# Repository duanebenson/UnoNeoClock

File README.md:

# UnoNeoClock
Arduino compatible NeoPixel clock design

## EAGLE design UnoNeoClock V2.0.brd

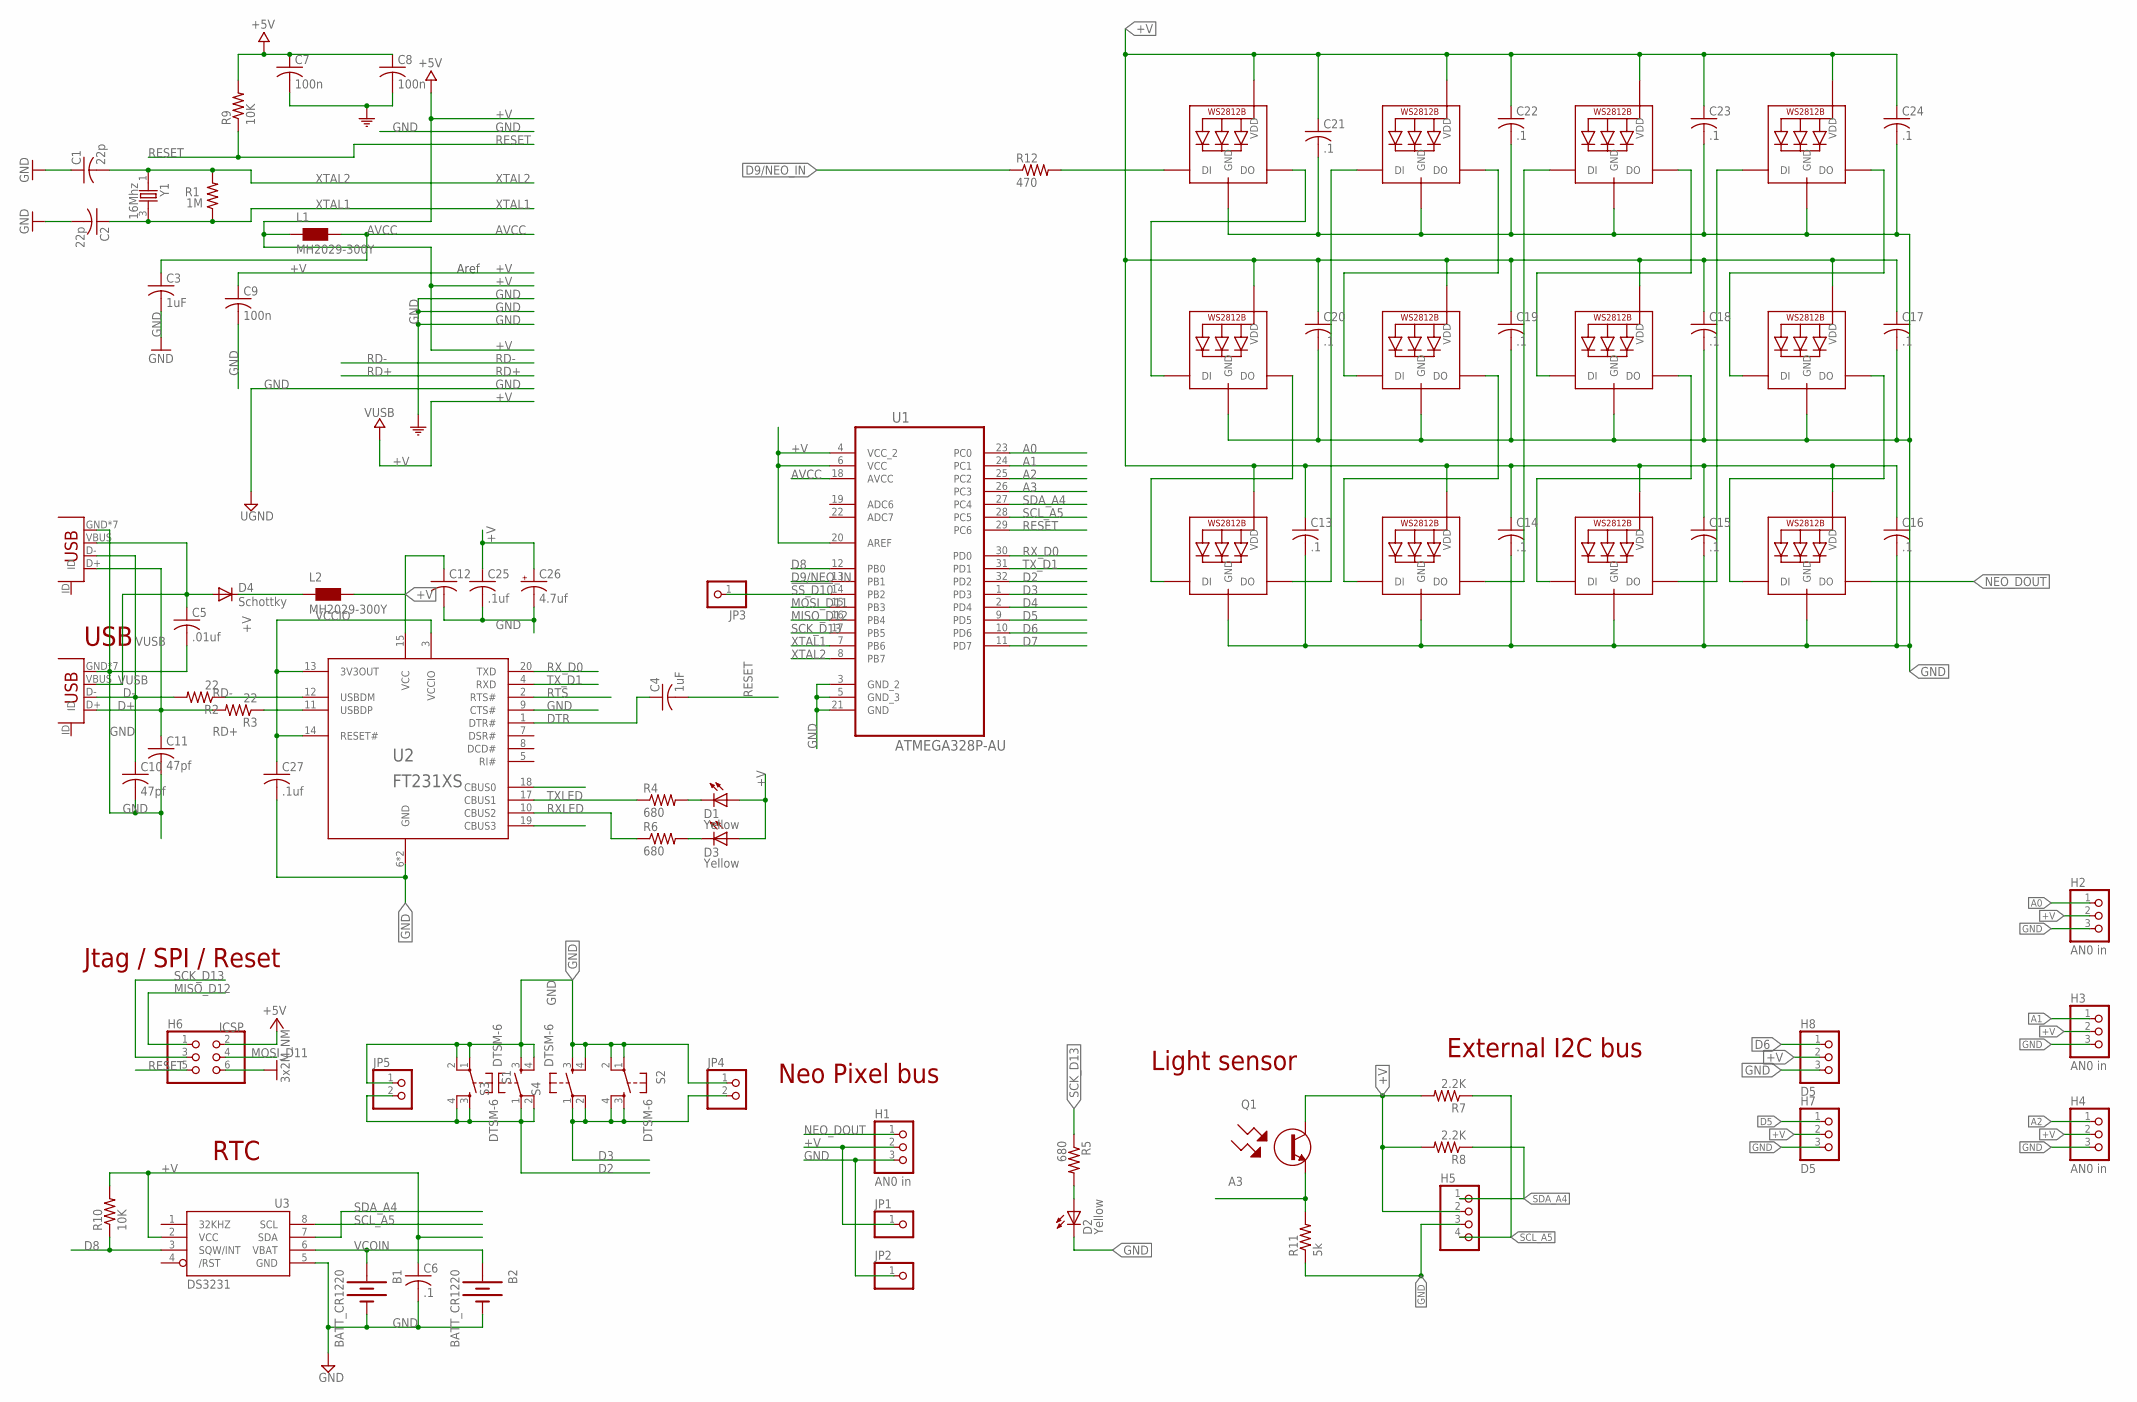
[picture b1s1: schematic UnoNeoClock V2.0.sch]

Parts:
B1, B2: BATT_CR1220; BATT_CR1220_HOLDER_SMT
C1, C2: 22p; C0805K
C3, C4: 1uF; C0805K
C5: .01uf; C0805K
C6, C13, C14, C15, C16, C17, C18, C19, C20, C21, C22, C23, C24: .1; C0805K
C7, C8, C9: 100n; C0805K
C10, C11: 47pf; C0805K
C12: C-USC1206K; C1206K
C25, C27: .1uf; C0805K
C26: 4.7uf; SMC_P
D1, D2, D3: Yellow; CHIP-LED0805
D4: Schottky; SOD123
H1, H2, H3, H4: AN0 in; 1X03-S
H5: PINHD-1X04_2.54-S; 1X04-S
H6: ICSP; 2X03
H7, H8: D5; 1X03-S
J1, J2: USB-MICRO-B-SMT/TH; USB-MICRO-B-SMT
JP1, JP2, JP3: PINHD-1X1; 1X01
JP4, JP5: PINHD-1X02_2.54-S; 1X02-S
L1, L2: MH2029-300Y; 0805
LED1, LED2, LED3, LED4, LED5, LED6, LED7, LED8, LED9, LED10, LED11, LED12: WS2812B5050; WS2812B
Q1: KDT00030FSTR; PT0603
R1: 1M; R0805
R2, R3: 22; R0805
R4, R5, R6: 680; R0805
R7, R8: 2.2K; R0805
R9, R10: 10K; R0805
R11: 5k; R0805
R12: 470; R0805
S1, S2, S3, S4: DTSM-6
U1: ATMEGA328P-AU; QFP80P900X900X120-32N
U2: FT231XS; SSOP20
U3: DS3231; SOIC8
Y1: 16Mhz; 3X5XTAL-SMT

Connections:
!SS_D10: JP3.1, U1.14 (PB2)
+V: C6.1, C7.1, C8.1, C9.1, C12.1, C13.1, C14.1, C15.1, C16.1, C17.1, C18.1, C19.1, C20.1, C21.1, C22.1, C23.1, C24.1, C25.1, C26.+, D1.A, D3.A, H1.2, H2.2, H3.2, H4.2, H5.2, H6.2, H7.2, H8.2, JP1.1, L1.1, L2.2, LED1.1-VDD (VDD), LED2.1-VDD (VDD), LED3.1-VDD (VDD), LED4.1-VDD (VDD), LED5.1-VDD (VDD), LED6.1-VDD (VDD), LED7.1-VDD (VDD), LED8.1-VDD (VDD), LED9.1-VDD (VDD), LED10.1-VDD (VDD), LED11.1-VDD (VDD), LED12.1-VDD (VDD), Q1.C, R7.2, R8.2, R9.2, R10.2, U1.4 (VCC_2), U1.6 (VCC), U1.20 (AREF), U2.15 (VCC), U3.2 (VCC)
A0: H2.1, U1.23 (PC0)
A1: H3.1, U1.24 (PC1)
A2: H4.1, U1.25 (PC2)
A3: Q1.E, R11.2, U1.26 (PC3)
AVCC: C3.1, L1.2, U1.18 (AVCC)
D2: JP5.2, S1.3, S1.4, S3.1, S3.2, U1.32 (PD2)
D3: JP4.2, S2.3, S2.4, S4.1, S4.2, U1.1 (PD3)
D4: U1.2 (PD4)
D5: H7.1, U1.9 (PD5)
D6: H8.1, U1.10 (PD6)
D7: U1.11 (PD7)
D8: R10.1, U1.12 (PB0), U3.3 (SQW/INT)
D9/NEO_IN: R12.1, U1.13 (PB1)
D+: C11.1, J1.D+, J2.D+, R3.2
D-: C10.1, J1.D-, J2.D-, R2.2
DTR: C4.1, U2.1 (DTR#)
GND: B1.1 (-), B2.1 (-), C1.1, C2.2, C3.2, C5.2, C6.2, C7.2, C8.2, C9.2, C10.2, C11.2, C12.2, C13.2, C14.2, C15.2, C16.2, C17.2, C18.2, C19.2, C20.2, C21.2, C22.2, C23.2, C24.2, C25.2, C26.-, C27.2, D2.C, H1.3, H2.3, H3.3, H4.3, H5.3, H6.6, H7.3, H8.3, J1.GND, J1.GND@1 (GND), J1.GND@2 (GND), J1.GND@3 (GND), J1.GND@4 (GND), J1.GND@5 (GND), J1.GND@6 (GND), J2.GND, J2.GND@1 (GND), J2.GND@2 (GND), J2.GND@3 (GND), J2.GND@4 (GND), J2.GND@5 (GND), J2.GND@6 (GND), JP2.1, JP4.1, JP5.1, LED1.3-GND (GND), LED2.3-GND (GND), LED3.3-GND (GND), LED4.3-GND (GND), LED5.3-GND (GND), LED6.3-GND (GND), LED7.3-GND (GND), LED8.3-GND (GND), LED9.3-GND (GND), LED10.3-GND (GND), LED11.3-GND (GND), LED12.3-GND (GND), R11.1, S1.1, S1.2, S2.1, S2.2, S3.3, S3.4, S4.3, S4.4, U1.3 (GND_2), U1.5 (GND_3), U1.21 (GND), U2.6 (GND), U2.9 (CTS#), U2.16 (GND), U3.5 (GND)
MISO_D12: H6.1, U1.16 (PB4)
MOSI_D11: H6.4, U1.15 (PB3)
unnamed: D2.A, R5.2
unnamed: D3.C, R6.2
unnamed: D1.C, R4.2
unnamed: LED1.2-DOUT (DO), LED2.4-DIN (DI)
unnamed: D4.C, L2.1
unnamed: LED2.2-DOUT (DO), LED3.4-DIN (DI)
unnamed: LED3.2-DOUT (DO), LED4.4-DIN (DI)
unnamed: LED4.2-DOUT (DO), LED5.4-DIN (DI)
unnamed: LED5.2-DOUT (DO), LED6.4-DIN (DI)
unnamed: LED6.2-DOUT (DO), LED7.4-DIN (DI)
unnamed: LED7.2-DOUT (DO), LED8.4-DIN (DI)
unnamed: LED8.2-DOUT (DO), LED9.4-DIN (DI)
unnamed: LED9.2-DOUT (DO), LED10.4-DIN (DI)
unnamed: LED10.2-DOUT (DO), LED11.4-DIN (DI)
unnamed: LED11.2-DOUT (DO), LED12.4-DIN (DI)
unnamed: LED1.4-DIN (DI), R12.2
NEO_DOUT: H1.1, LED12.2-DOUT (DO)
RD+: R3.1, U2.11 (USBDP)
RD-: R2.1, U2.12 (USBDM)
RESET: C4.2, H6.5, R9.1, U1.29 (PC6)
RTS: U2.2 (RTS#)
RXLED: R6.1, U2.10 (CBUS2)
RX_D0: U1.30 (PD0), U2.20 (TXD)
SCK_D13: H6.3, R5.1, U1.17 (PB5)
SCL_A5: H5.4, R7.1, U1.28 (PC5), U3.8 (SCL)
SDA_A4: H5.1, R8.1, U1.27 (PC4), U3.7 (SDA)
TXLED: R4.1, U2.17 (CBUS1)
TX_D1: U1.31 (PD1), U2.4 (RXD)
VCCIO: C27.1, U2.3 (VCCIO), U2.13 (3V3OUT), U2.14 (RESET#)
VCOIN: B1.3 (+), B2.3 (+), U3.6 (VBAT)
VUSB: C5.1, D4.A, J1.VBUS, J2.VBUS
XTAL1: C2.1, R1.1, U1.7 (PB6), Y1.3 (2)
XTAL2: C1.2, R1.2, U1.8 (PB7), Y1.1

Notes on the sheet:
USB
External I2C bus
Jtag / SPI / Reset
RTC
Neo Pixel bus
Aref
Light sensor

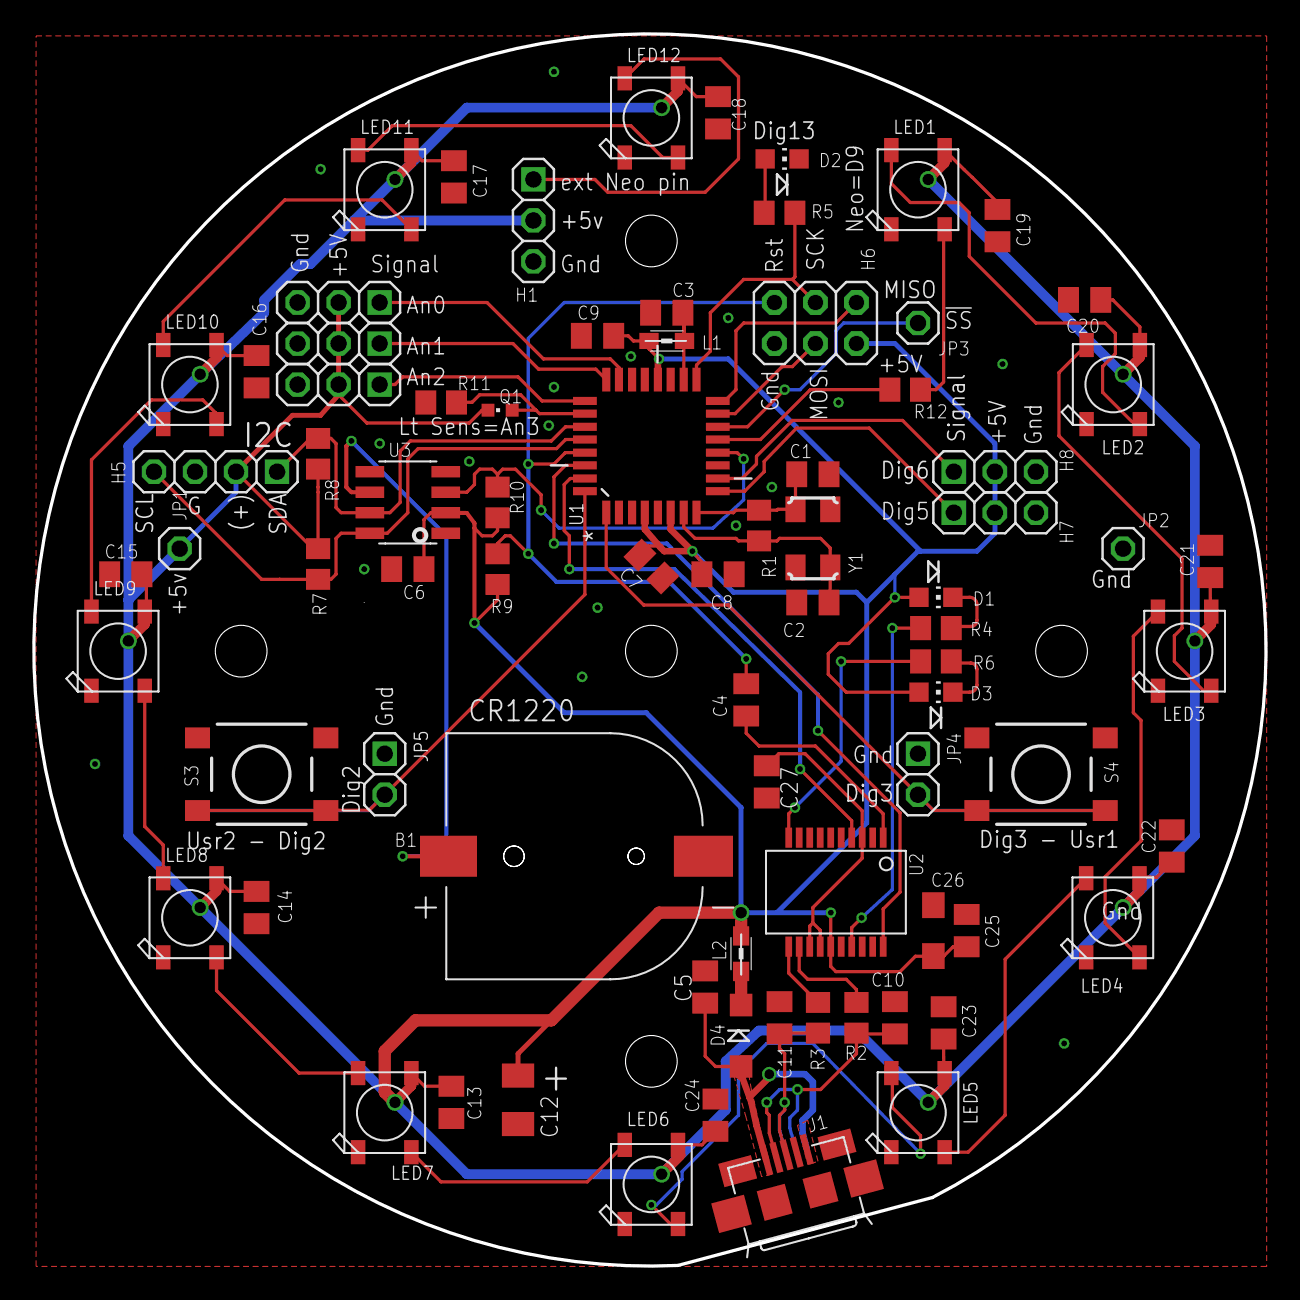
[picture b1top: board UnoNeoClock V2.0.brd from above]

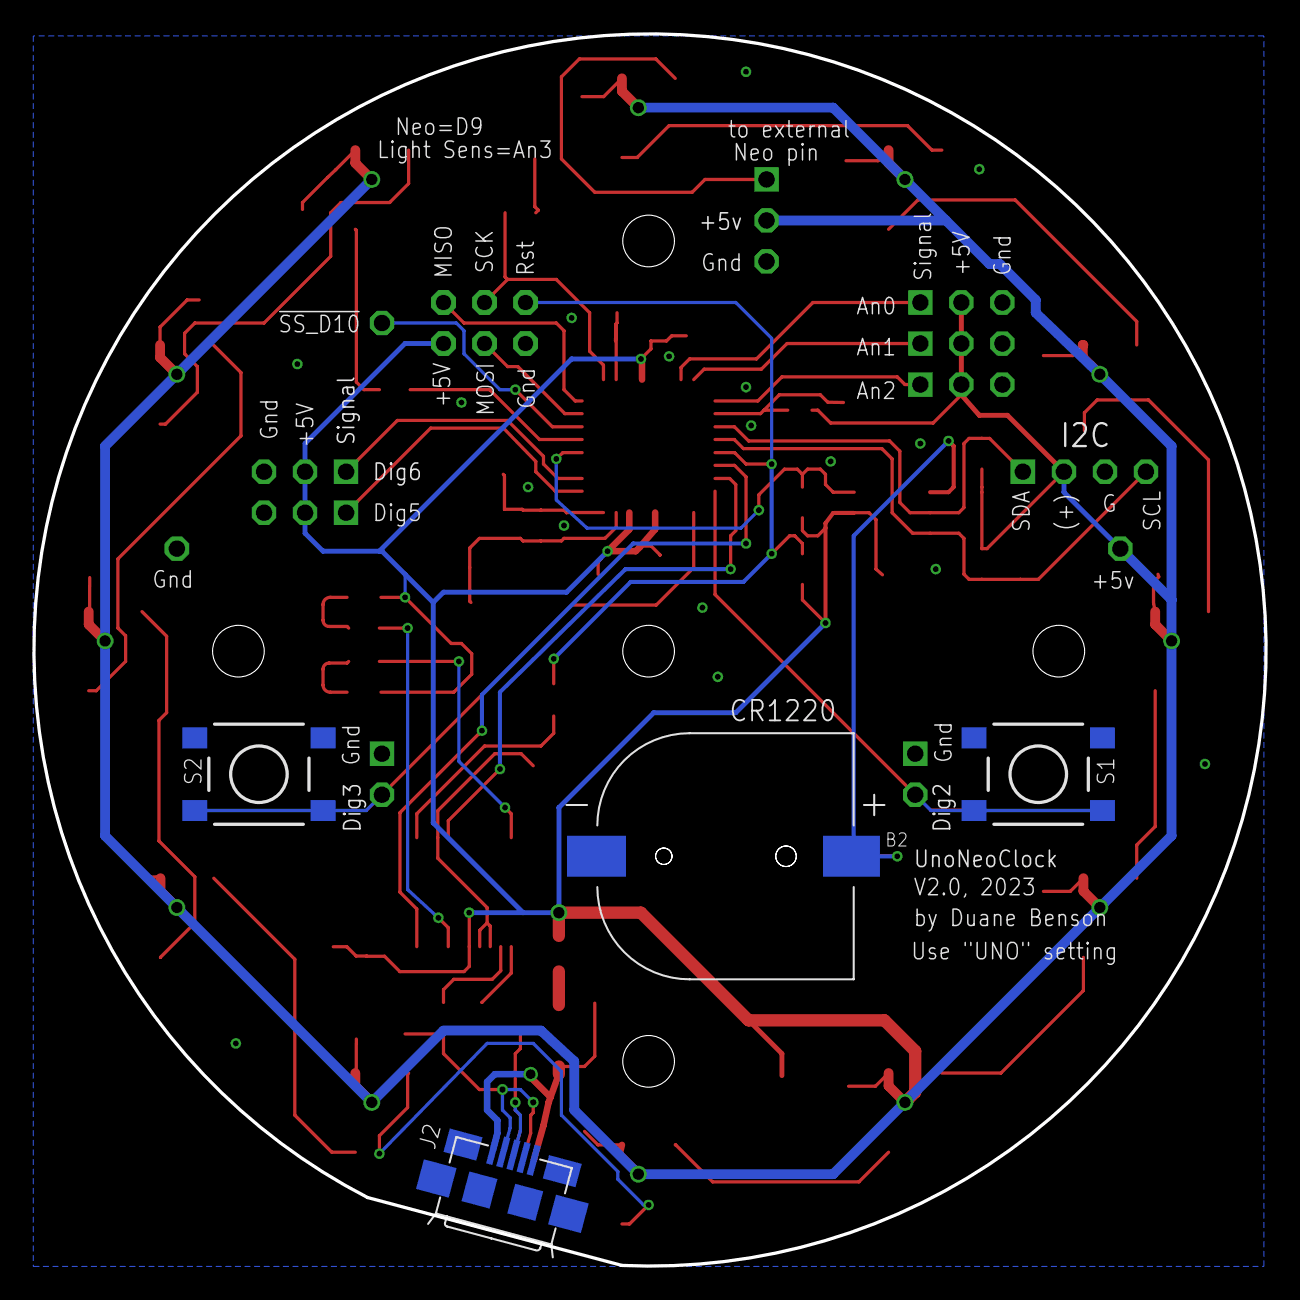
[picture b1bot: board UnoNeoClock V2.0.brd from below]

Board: 2 copper layers, 76.3 x 76.3 mm, 95 parts (4 on the bottom side), 51 nets.

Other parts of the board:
U$1, U$2, U$4, U$5, U$6, U$7, U$8, U$9, U$10, U$11, U$12, U$13: CLOCKPOSITION

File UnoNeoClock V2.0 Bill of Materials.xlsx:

Item # | Qty | Ref Des | Manufacturer | Manf part num | Distributor | Distributor Part number | Description | Package | Type
1 | 1 | U1 | Atmel | ATMEGA328P-AUR | Digikey | ATMEGA328P-AURCT-ND | MCU | 44-TQFP | SMT
2 | 1 | U2 | FTDI | FT231XS-R | Digikey | 768-1129-1-ND | USB to UART | 20-SSOP | SMT
3 | 1 | U3 | Maxim | DS3231MZ+ | Digikey | DS3231MZ+-ND | RTC | 8-SOIC | SMT
4 | 1 | Q1 | Fairchild | KDT00030TR | Digikey | KDT00030FSCT-ND | Phototransistor | 0603 | SMT
5 | 1 | Y1 | Epson | NX5032GC-16MHZ-STD-CSK-6 | Digikey | 644-1194-1-ND | 16 MHz |  | SMT
6 | 3 | D1, D2, D3 | Osram | LY R976-PS-36 | Digikey | 475-2560-1-ND | LED Yellow | 0805 | SMT
7 | 1 | D4 | Diodes, Inc | B0520LW-7-F | Digikey | B0520LW-FDICT-ND | Schottky | 0805 | SMT
 |  | D5 |  |  |  |  | TVS
8 | 2 | C1, C2 | Yageo | CC0805DRNPO9BN8R0 | Digikey | 311-1097-1-ND | 8pf | 0805 | SMT
9 | 2 | C3, C4 | Yageo | CC0805KKX7R7BB105 | Digikey | 311-1365-1-ND | 1.0uf | 0805 | SMT
10 | 1 | C5 | Yageo | CC0805KRX7R9BB103 | Digikey | 311-1136-1-ND | .01uf | 0805 | SMT
11 | 17 | C6, C7, C8, C9, C13-C25 | Samsung | CL21B104KOANNNC | Digikey | 1276-2448-1-ND | .1uf | 0805 | SMT
12 | 2 | C10, C11 | Samsung | CL21C470JBANNNC | Digikey | 1276-1156-1-ND | 47pf | 0805 | SMT
13 | 1 | C12 | AVX | F931A476MAA | Digikey | 478-8225-1-ND | 47uf |  | SMT
14 | 1 | C26 | Taiyo | LMK212BJ475KD-T | Digikey | 587-1297-1-ND | 4.7uf | 0805 | SMT
15 | 2 | L1, L2 | Bourns | MH2029-300Y | Digikey | MH2029-300YCT-ND | 30ohm ferrite | 0805 | SMT
16 | 1 | R1 | Stackpole | RMCF0805JT1M00 | Digikey | RMCF0805JT1M00CT-ND | 1M | 0805 | SMT
17 | 2 | R2, R3 | Stackpole | RMCF0805JT22R0 | Digikey | RMCF0805JT22R0CT-ND | 22 ohms | 0805 | SMT
18 | 3 | R4, R5, R6 | Stackpole | RMCF0805FT680R | Digikey | RMCF0805FT680RCT-ND | 680 ohm | 0805 | SMT
19 | 2 | R7, R8 | Rohm | MCR10ERTF2201 | Digikey | RHM2.20KCHCT-ND | 2.2K | 0805 | SMT
20 | 2 | R9, R10 | Stackpole | RMCF0805FT10K0 | Digikey | RMCF0805FT10K0CT-ND | 10K | 0805 | SMT
21 | 1 | R11 | Stackpole | RMCF0805JT4K70 | Digikey | RMCF0805JT4K70CT-ND | 4.7K | 0805 | SMT
 |  | R12 |  |  |  |  | 470 | 0805 | SMT
22 |  | S1, S2 | C&K | PTS645SM43SMTR92 LFS | Digikey | CKN9112CT-ND | Momentary push |  | DNS
23 | 2 | S3, S4 | C&K | PTS645SM43SMTR92 LFS | Digikey | CKN9112CT-ND | Momentary push |  | SMT
24 |  | J1 | FCI | 10118192-0001LF | Digikey | 609-4613-1-ND | USB microB |  | DNS
25 | 1 | J2 | FCI | 10118192-0001LF | Digikey | 609-4613-1-ND | USB microB |  | SMT
26 | 1 | B1 | Linx | BC501SM | Digikey | BC501SM-ND | 12mm Coin cell |  | SMT
27 |  | B2 | Linx | BC501SM | Digikey | BC501SM-ND | 12mm Coin cell |  | DNS
28 | 12 | LED1 - LED12 | Adafruit | 1655 | Digikey | 1528-1104-ND |  |  | SMT
29 | 4 |  | Adafruit | 1768 | Adafruit | ID: 1768 | 1/4 pixel ring |  | DNS
 |  |  |  |  |  |  |  |  | Assembly summary
 |  |  |  |  |  |  |  | BOM line items | 22
 |  |  |  |  |  |  |  | SMT | 64
 |  |  |  |  |  |  |  | BGA | 0
 |  |  |  |  |  |  |  | Thru-hole | 0
 |  |  |  |  |  |  |  | Other | 0

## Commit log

2023-12-08 Update UnoNeoClock_V2.0.ino
    Corrected some minor typos in the comments. No code changes
